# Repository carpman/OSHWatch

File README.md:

Open Source Hardware watch project

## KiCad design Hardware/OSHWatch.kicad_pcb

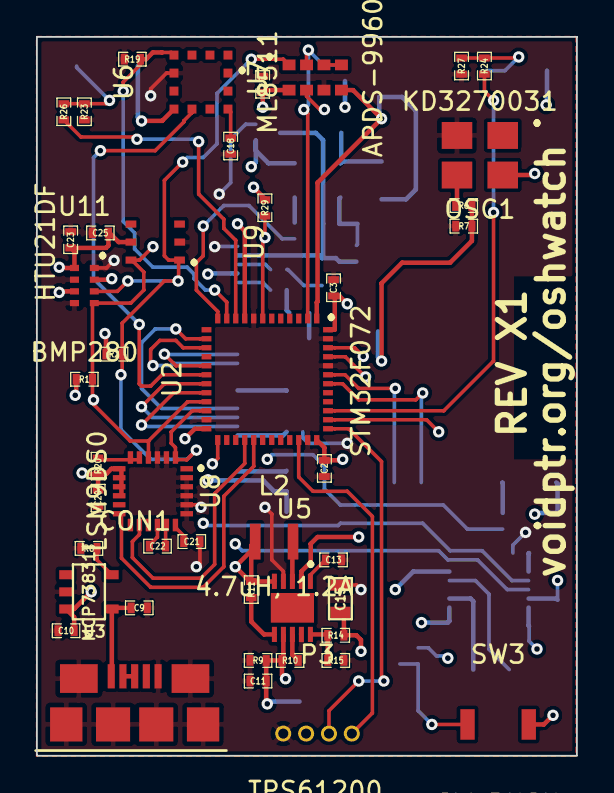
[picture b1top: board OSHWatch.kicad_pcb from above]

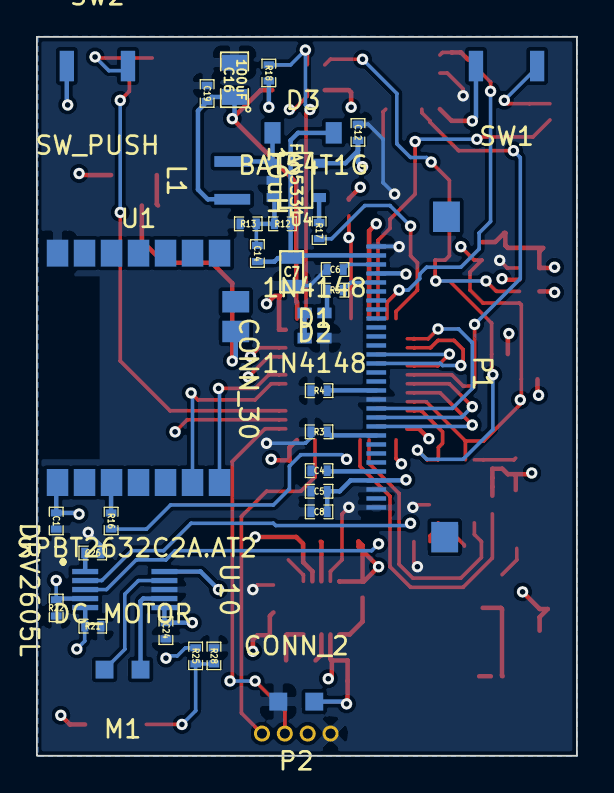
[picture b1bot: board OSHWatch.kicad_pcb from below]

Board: 4 copper layers, 30.0 x 39.9 mm, 80 parts (36 on the bottom side), 61 nets.

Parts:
C1, C2, C5, C8, C9, C10, C11, C20: 10uF; SM0402
C3: 100pF; SM0402
C4, C6, C26: 1uF; SM0402
C7: 10uF,16V; SM0603
C12: 10uF,6.3V; SM0402
C13, C24: 0.1uF; SM0402
C14: 0.1uF,16V; SM0402
C15: 22uF; SM0603
C16: 100uF; SM0805
C17, C19: 1uf; SM0402
C18: 1nF; SM0402
C21: 4.7uF; SM0402
C22: .22uF; SM0402
C23, C25: 100nF; SM0402
CON1: USB-MINI-B; 10118192
D1, D2: 1N4148; SOD-523
D3: BAT54T1G; SOD-123
L1: 10uH; 2518
L2: 4.7uH, 1.2A; 2518
M1: DC_MOTOR; 2PAD
OSC1: KD3270031
P1: CONN_30; XF2M-3015-1A
P2: CONN_2; 2PAD
P3: CONN_4; 4pin
R1, R2: 4.7K; SM0402
R3: 600K; SM0402
R4, R6, R7, R13, R16, R17, R18, R20, R23, R24, R25, R26, R27, R28, R29: 10K; SM0402
R5: 50; SM0402
R8: 2K; SM0402
R9, R15: 220K; SM0402
R10, R11: 10k; SM0402
R12: 100K; SM0402
R14: 1.2M; SM0402
R19, R21, R22: 200k; SM0402
SW1, SW2, SW3: SW_PUSH; B3U-3000P
U1: SPBT2632C2A.AT2; SPBT2632C2A
U2: STM32F072; UFQFPN48
U3: MCP73831T; SOT23-5
U4: FAN5331; SOT23-5
U5: TPS61200; VSON-10
U6: ML8511
U7: APDS-9960
U8: LSM9DS0
U9: HTU21DF; HTU12DF
U10: DRV2605L; VSSOP-10
U11: BMP280

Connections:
+3.3V: C1.1, C2.1, C3.1, C5.2, C8.2, C15.1, C17.1, C20.1, C23.1, C25.1, OSC1.4, P1.4, P1.27, R1.1, R2.1, R14.1, R18.2, R20.2, R29.1, SW1.2, SW2.1, SW3.2, U1.8, U2.9, U2.24, U2.36, U2.48, U5.2, U6.7, U7.8, U8.15, U8.16, U8.17, U8.18, U9.5, U11.2, U11.6, U11.8
+5V: C9.1, CON1.1, U3.4
+12V: C7.2, C14.1, D3.2, P1.2, R12.1
+BATT: C10.1, C11.1, C12.1, C16.1, C19.1, C24.1, L1.1, L2.1, P2.1, R9.1, R10.1, R11.1, U2.1, U3.3, U4.5, U5.5, U5.7, U7.5, U10.6, U10.10
/Bluetooth/32KHZ_CLK: OSC1.3, R6.2
/Bluetooth/BT_RESET: R16.2, U2.25
/Bluetooth/BT_RX_STM_TX: U1.13, U2.42
/Bluetooth/BT_TX_STM_RX: U1.14, U2.43
/Display/DISPLAY_CS: P1.19, U2.14
/Display/DISPLAY_DC: P1.20, U2.19
/Display/DISPLAY_MOSI: P1.13, U2.17
/Display/DISPLAY_RESET: P1.21, U2.20
/Display/DISPLAY_SCK: P1.14, U2.15
/Power/DISPLAY_BIAS_EN: R17.1, U2.12
/STM32F072/BUTTON_1: R26.2, U2.10
/STM32F072/BUTTON_2: R24.2, U2.39
/STM32F072/BUTTON_3: R25.2, U2.38
/STM32F072/GESTURE_INT: R18.1, U2.2, U7.2
/STM32F072/GYRO_INT: U2.28, U8.11
/STM32F072/I2C_SCK: R1.2, U2.21, U7.7, U8.21, U9.6, U10.2, U11.4
/STM32F072/I2C_SDA: R2.2, U2.22, U7.1, U8.24, U9.1, U10.3, U11.3
/STM32F072/NRST: P3.2, R29.2, U2.7
/STM32F072/UV_EN: R19.2, U2.11, U6.4
/STM32F072/UV_OUT: U2.18, U6.8
/STM32F072/VIB_EN: R21.2, U2.45, U10.5
/STM32F072/VIB_TRIG: R22.2, U2.46, U10.4
/STM32F072/XM_INT: U2.29, U8.13
GND: C1.2, C2.2, C3.2, C4.1, C5.1, C6.1, C7.1, C8.1, C9.2, C10.2, C11.2, C12.2, C13.2, C15.2, C16.2, C17.2, C18.2, C19.2, C20.2, C21.2, C23.2, C24.2, C25.2, C26.1, CON1.5, CON1.6, CON1.7, CON1.8, CON1.9, D1.2, OSC1.2, P1.1, P1.18, P1.28, P1.30, P2.2, P3.1, R3.1, R4.1, R7.2, R8.2, R9.2, R13.2, R15.2, R19.1, R21.1, R22.1, R23.1, R27.2, R28.2, U1.7, U2.8, U2.23, U2.35, U2.44, U2.47, U3.2, U4.2, U5.4, U5.9, U6.5, U7.6, U8.2, U8.3, U8.4, U8.5, U8.6, U8.22, U8.23, U9.2, U10.8, U11.1, U11.5, U11.7
unnamed: R16.1, U1.10
unnamed: R6.1, R7.1, U1.15
unnamed: P3.4, U2.34
unnamed: P3.3, U2.37
unnamed: P1.17, R4.2
unnamed: D1.1, D2.2
unnamed: D2.1, R5.1
unnamed: P1.5, R5.2
unnamed: C4.2, P1.26
unnamed: P1.22, R3.2
unnamed: C6.2, P1.3
unnamed: D3.1, L1.2, U4.1
unnamed: R8.1, U3.5
unnamed: R10.2, U5.8
unnamed: CON1.2, CON1.3
unnamed: C14.2, R12.2, R13.1, U4.3
unnamed: R17.2, U4.4
unnamed: R14.2, R15.1, U5.10
unnamed: C13.1, U5.1
unnamed: L2.2, U5.3
unnamed: R11.2, U5.6
unnamed: M1.2, U10.9
unnamed: M1.1, U10.7
unnamed: C18.1, U6.10
unnamed: R20.1, U8.19, U8.20
unnamed: C26.2, U10.1
unnamed: R24.1, R27.1, SW2.2
unnamed: R25.1, R28.1, SW3.1
unnamed: R23.2, R26.1, SW1.1
unnamed: C21.1, U8.7
unnamed: C22.1, U8.8
unnamed: U7.3, U7.4
unnamed: C22.2, U8.9

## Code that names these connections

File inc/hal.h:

#ifndef __hal_h__
#define __hal_h__


#define DISPLAY_DC_RESET_BANK   GPIOC
#define DISPLAY_RESET_PIN       GPIO_Pin_7
#define DISPLAY_DC_PIN          GPIO_Pin_8
#define DISPLAY_CS_PIN          GPIO_Pin_9


#define SPI_BANK                GPIOB
#define SPI_SCK_PIN             GPIO_Pin_3
#define SPI_MOSI_PIN            GPIO_Pin_5
#define SPI_MISO_PIN            GPIO_Pin_4

//PB13 sck
//PB14 data
#define I2C_BANK                GPIOB
#define I2C_SCK_PIN             GPIO_Pin_10
#define I2C_SDA_PIN             GPIO_Pin_11

#define UART_BANK               GPIOA
#define UART_TX_PIN             GPIO_Pin_9
#define UART_RX_PIN             GPIO_Pin_10
#define UART_CTS_PIN            GPIO_Pin_11
#define UART_RTS_PIN            GPIO_Pin_12

void Clock_Setup(void);
void SPI_Setup(void);
void I2C_Setup(void);
void UART_Setup(void);
void GPIO_Setup(void);

void I2C_WriteRegister(uint8_t addr, uint8_t reg, uint8_t val);
uint8_t I2C_ReadReg(uint8_t addr, uint8_t reg, uint8_t *buffer, uint8_t length);

uint8_t uart_recieve_string(char *dest, uint8_t length);
void uart_send_string(char *string);
uint8_t uart_receive_string_until(char *dest, uint8_t length, unsigned char stop);

void Delay(uint32_t Time);

#endif

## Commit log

2015-06-08 Clear Readme
2015-06-08 Move uart functions to hal, clean up some warnings
2015-06-14 Start the hardware design
2015-06-14 Begin on the schematic and footprints
2015-06-15 Adding sensors
2015-06-23 Powering directly from battery won't work due to needing to run duing a charge cycle. Added 3.3v regulator, battery management, resistor divider for sensing battery voltage.
2015-06-23 Connect sense line to STM32
2015-06-25 Working on display bias dc-to-dc
2015-06-29 Nearly completed schematic
2015-07-02 More packages, including schematic
2015-07-05 Initial layout complete
2015-07-07 Footprint corrections
2015-07-08 Final footprint corrections, gerbers
2015-07-09 Rev X1 Gerbers
